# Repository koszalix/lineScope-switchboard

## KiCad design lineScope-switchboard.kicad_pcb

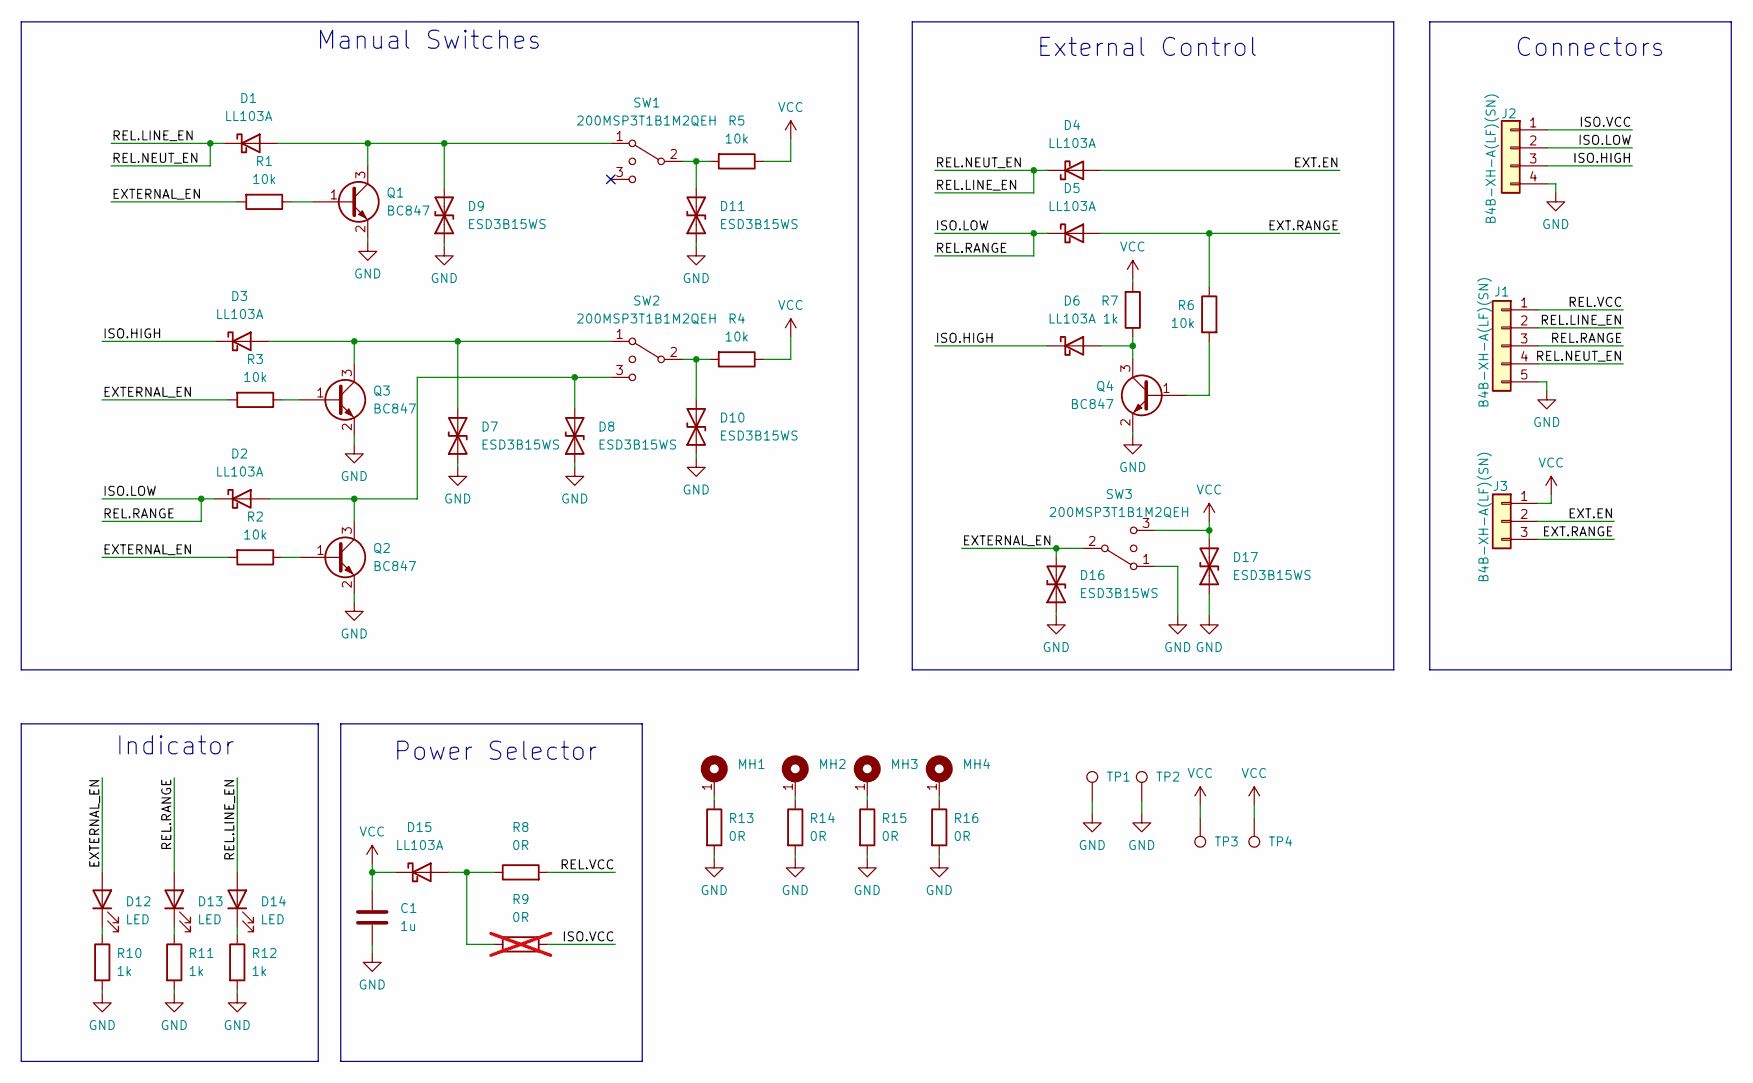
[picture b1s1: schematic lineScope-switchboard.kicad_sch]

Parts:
C1: 1u; C_0603_1608Metric; Tolerance 10%; Rated voltage 50V; MPN 0603B105K500CT
D1, D2, D3, D4, D5, D6, D15: LL103A; D_MiniMELF; MPN LL103A
D7, D8, D9, D10, D11, D16, D17: ESD3B15WS; D_SOD-323_HandSoldering
D12, D13, D14: LED; LED_D5.0mm_FlatTop
J1: B4B-XH-A(LF)(SN); JST_XH_B5B-XH-A_1x05_P2.50mm_Vertical
J2: B4B-XH-A(LF)(SN); JST_XH_B4B-XH-A_1x04_P2.50mm_Vertical
J3: B4B-XH-A(LF)(SN); JST_XH_B3B-XH-A_1x03_P2.50mm_Vertical
MH1, MH2, MH3, MH4: MountingHole_3.2mm_M3_Pad
Q1, Q2, Q3, Q4: BC847; SOT-23
R1, R2, R3, R4, R5, R6: 10k; R_0603_1608Metric; Tolerance 1%; MPN RC0603FR-0710k
R7, R10, R11, R12: 1k; R_0603_1608Metric; Tolerance 1%; MPN RC0603FR-071k
R8, R13, R14, R15, R16: 0R; R_0603_1608Metric; Tolerance 1%; MPN RC0603FR-070R
R9: 0R; R_0603_1608Metric; Tolerance 1%; MPN RC0603FR-070R; not fitted
SW1, SW2, SW3: 200MSP3T1B1M2QEH; ESWITCH-100SP1T1B1M1QEH; MPN 200MSP3T1B1M2QEH
TP1, TP2, TP3, TP4: TestPoint; TestPoint_Pad_D1.0mm

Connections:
/EXT.EN: D4.2 (A), J3.2
/EXT.RANGE: D5.2 (A), J3.3, R6.1
/EXTERNAL_EN: D12.2 (A), D16.2 (A2), R1.2, R2.2, R3.2, SW3.2
/ISO.HIGH: D3.1 (K), D6.1 (K), J2.3
/ISO.LOW: D2.1 (K), D5.1 (K), D13.2 (A), J1.3, J2.2
/ISO.VCC: J2.1, R9.2
/REL.LINE_EN: D1.1 (K), D4.1 (K), D14.2 (A), J1.2, J1.4
/REL.VCC: J1.1, R8.2
GND: C1.2, D7.1 (A1), D8.1 (A1), D9.1 (A1), D10.1 (A1), D11.1 (A1), D16.1 (A1), D17.1 (A1), J1.5, J2.4, Q1.2 (E), Q2.2 (E), Q3.2 (E), Q4.2 (E), R10.2, R11.2, R12.2, R13.2, R14.2, R15.2, R16.2, SW3.1, TP1.1, TP2.1
unnamed: D1.2 (A), D9.2 (A2), Q1.3 (C), SW1.1
unnamed: D2.2 (A), D8.2 (A2), Q2.3 (C), SW2.3
unnamed: D3.2 (A), D7.2 (A2), Q3.3 (C), SW2.1
unnamed: D6.2 (A), Q4.3 (C), R7.1
unnamed: D10.2 (A2), R4.2, SW2.2
unnamed: D11.2 (A2), R5.2, SW1.2
unnamed: D12.1 (K), R10.1
unnamed: D13.1 (K), R11.1
unnamed: D14.1 (K), R12.1
unnamed: D15.2 (A), R8.1, R9.1
unnamed: MH1.1, R13.1
unnamed: MH2.1, R14.1
unnamed: MH3.1, R15.1
unnamed: MH4.1, R16.1
unnamed: Q1.1 (B), R1.1
unnamed: Q2.1 (B), R2.1
unnamed: Q3.1 (B), R3.1
unnamed: Q4.1 (B), R6.2
VCC: C1.1, D15.1 (K), D17.2 (A2), J3.1, R4.1, R5.1, R7.2, SW3.3, TP3.1, TP4.1

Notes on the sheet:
External Control
Power Selector
Indicator
Connectors
Manual Switches

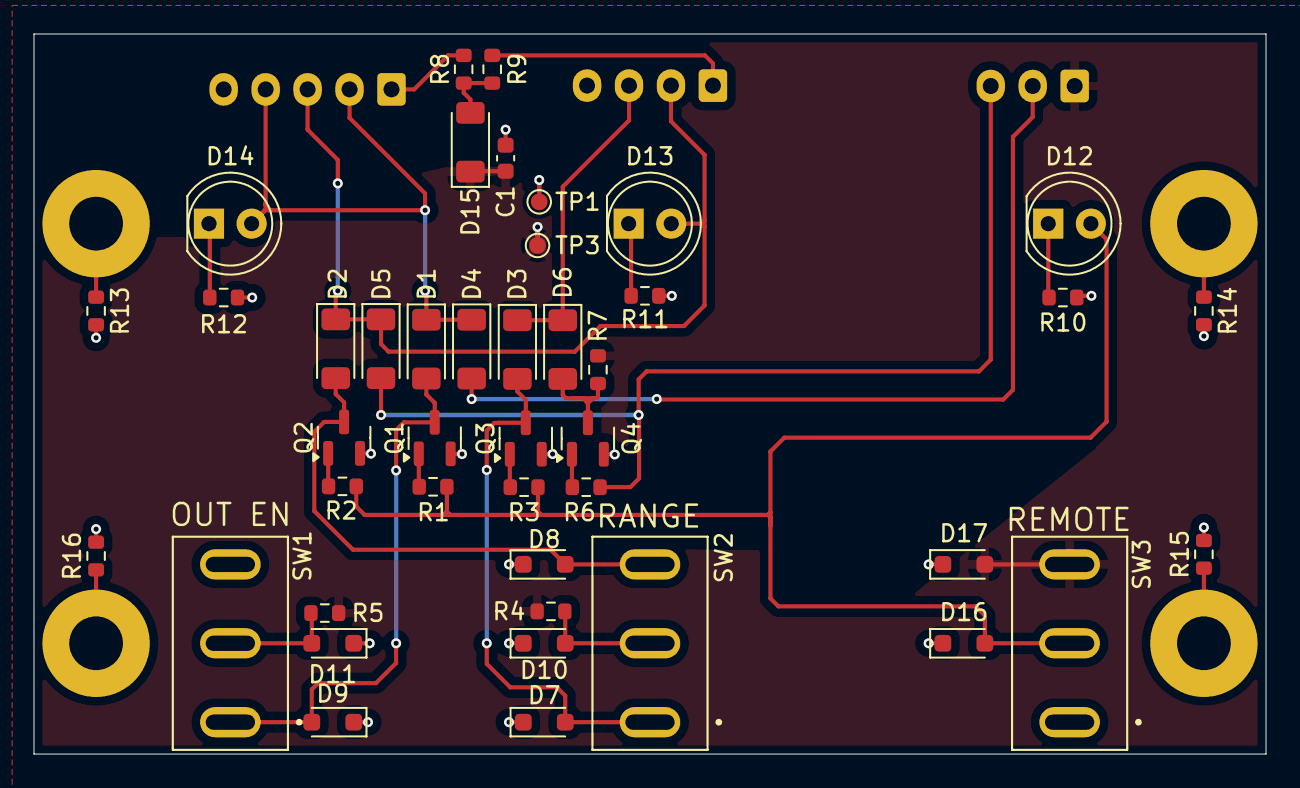
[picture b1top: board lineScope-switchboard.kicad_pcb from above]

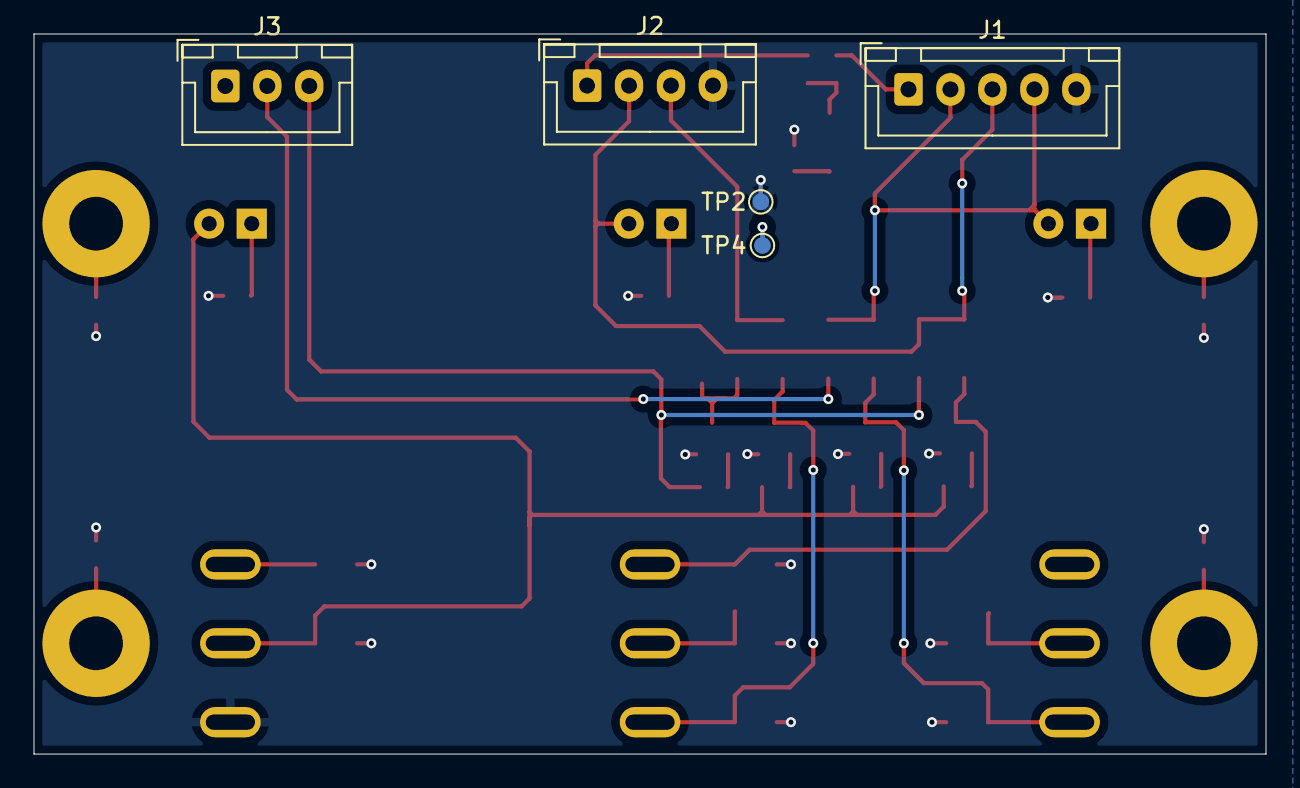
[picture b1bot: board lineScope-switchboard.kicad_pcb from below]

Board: 2 copper layers, 73.4 x 42.9 mm, 52 parts (5 on the bottom side), 28 nets.
